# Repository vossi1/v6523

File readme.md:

# V6523 - Replacement for a 6523 or 6525 without IRQ Controller (CBM2 keyboard TPI)  

**Copyright (c) 2024 Vossi - v.1 / v.2 (C64 IEEE option)**

**www.mos6509.com**

## License
This work is licensed under a Creative Commons Attribution-ShareAlike 4.0
International License. See [https://creativecommons.org/licenses/by-sa/4.0/](https://creativecommons.org/licenses/by-sa/4.0/).

:thumbsup: v.2 now with C64 IEEE488 Interface support (use special IEEE hdl-code)!

:pushpin: At JLC you have to select: Remove Order Number = "Specify a location"

**[Schematic](https://github.com/vossi1/v6523/blob/master/v6523_v2.png)**

**[Parts](https://github.com/vossi1/v6523/blob/master/parts.txt)**

**CPLD-Firmware:** The .JED file can be uploaded with a JTAG-SMT2 Xilinx programmer (China) and [xc3sprog](https://xc3sprog.sourceforge.net/)

:exclamation: **BEWARE: I got good CPLD's from China but there are some XC9572XL FAKES out there**

cbm 720 (the very first V6523 on the photo misses the pin1 side notch)

:white_check_mark: **Tested successful in cbm620, 720 and P500 with:** Diagnostic-ROM and my fingers :wink:

:x: **Does not work in 1551, C64-Magic Voice, CDTV (A570)**

You have to solder a wire to pin 10 of the 74LS08 (PHI2): (sadly I forgot the "specify a location" option :wink: )

I added this logic for the IEEE support to the v.2 version:

REASON: Commodore didn't combined CS with PHI2 like in the CBM2 machines.
According to the datasheet for the 6525, they should have done that.
I don't know why it still works with the 6525 in the IEEE interface?

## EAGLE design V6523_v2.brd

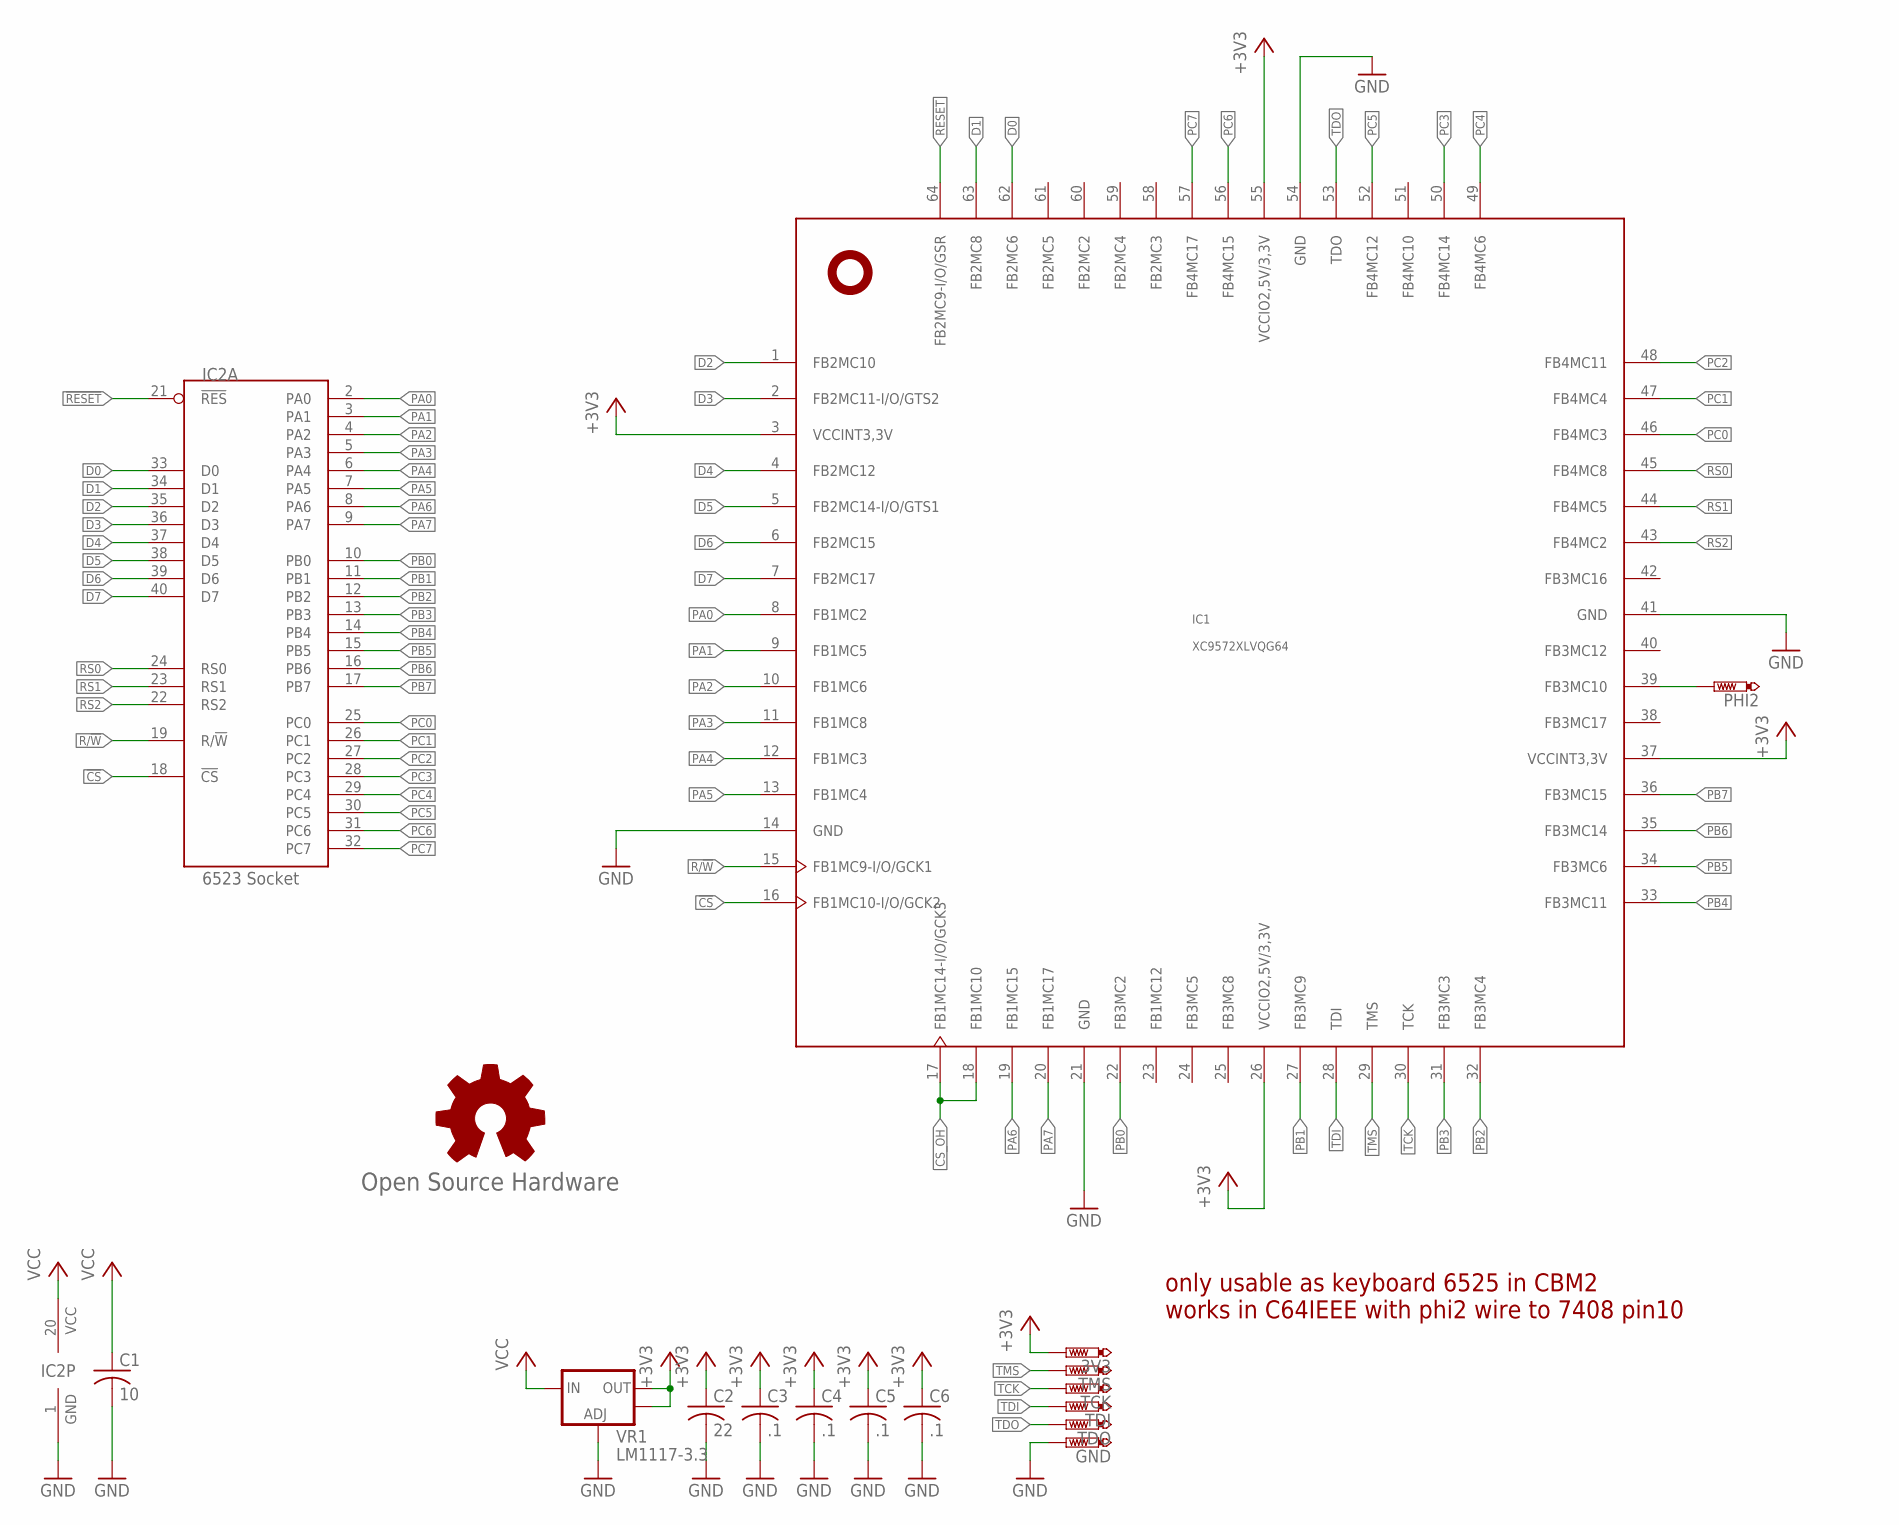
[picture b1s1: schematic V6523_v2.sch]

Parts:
3V3: PTR1TP08R; TP08R
C1: 10; C0805
C2: 22; C0805
C3, C4, C5, C6: .1; C0603
GND: PTR1TP08R; TP08R
GOLD_ORB_SM1: Open Source Hardware; OSHW_5MM
IC1: XC9572XLVQG64; VQFP64
IC2: 6523 Socket; DIL40-RP-NOFRAME
PHI2: PTR1TP08R; TP08R
TCK: PTR1TP08R; TP08R
TDI: PTR1TP08R; TP08R
TDO: PTR1TP08R; TP08R
TMS: PTR1TP08R; TP08R
VR1: LM1117-3.3; SOT223

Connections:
!CS: IC1.16 (FB1MC10-I/O/GCK2), IC2.18 (!CS)
!RESET: IC1.64 (FB2MC9-I/O/GSR), IC2.21 (!RES)
+3V3: 3V3.TP, C2.1, C3.1, C4.1, C5.1, C6.1, IC1.3 (VCCINT3,3V), IC1.26 (VCCIO2,5V/3,3V), IC1.37 (VCCINT3,3V), IC1.55 (VCCIO2,5V/3,3V), VR1.2 (OUT), VR1.4 (OUT)
CS_OH: IC1.17 (FB1MC14-I/O/GCK3), IC1.18 (FB1MC10)
D0: IC1.62 (FB2MC6), IC2.33 (D0)
D1: IC1.63 (FB2MC8), IC2.34 (D1)
D2: IC1.1 (FB2MC10), IC2.35 (D2)
D3: IC1.2 (FB2MC11-I/O/GTS2), IC2.36 (D3)
D4: IC1.4 (FB2MC12), IC2.37 (D4)
D5: IC1.5 (FB2MC14-I/O/GTS1), IC2.38 (D5)
D6: IC1.6 (FB2MC15), IC2.39 (D6)
D7: IC1.7 (FB2MC17), IC2.40 (D7)
GND: C1.2, C2.2, C3.2, C4.2, C5.2, C6.2, GND.TP, IC1.14 (GND), IC1.21 (GND), IC1.41 (GND), IC1.54 (GND), IC2.1 (GND), VR1.1 (ADJ)
PA0: IC1.8 (FB1MC2), IC2.2 (PA0)
PA1: IC1.9 (FB1MC5), IC2.3 (PA1)
PA2: IC1.10 (FB1MC6), IC2.4 (PA2)
PA3: IC1.11 (FB1MC8), IC2.5 (PA3)
PA4: IC1.12 (FB1MC3), IC2.6 (PA4)
PA5: IC1.13 (FB1MC4), IC2.7 (PA5)
PA6: IC1.19 (FB1MC15), IC2.8 (PA6)
PA7: IC1.20 (FB1MC17), IC2.9 (PA7)
PB0: IC1.22 (FB3MC2), IC2.10 (PB0)
PB1: IC1.27 (FB3MC9), IC2.11 (PB1)
PB2: IC1.32 (FB3MC4), IC2.12 (PB2)
PB3: IC1.31 (FB3MC3), IC2.13 (PB3)
PB4: IC1.33 (FB3MC11), IC2.14 (PB4)
PB5: IC1.34 (FB3MC6), IC2.15 (PB5)
PB6: IC1.35 (FB3MC14), IC2.16 (PB6)
PB7: IC1.36 (FB3MC15), IC2.17 (PB7)
PC0: IC1.46 (FB4MC3), IC2.25 (PC0)
PC1: IC1.47 (FB4MC4), IC2.26 (PC1)
PC2: IC1.48 (FB4MC11), IC2.27 (PC2)
PC3: IC1.50 (FB4MC14), IC2.28 (PC3)
PC4: IC1.49 (FB4MC6), IC2.29 (PC4)
PC5: IC1.52 (FB4MC12), IC2.30 (PC5)
PC6: IC1.56 (FB4MC15), IC2.31 (PC6)
PC7: IC1.57 (FB4MC17), IC2.32 (PC7)
PHI2: IC1.39 (FB3MC10), PHI2.TP
R/!W: IC1.15 (FB1MC9-I/O/GCK1), IC2.19 (R/!W)
RS0: IC1.45 (FB4MC8), IC2.24 (RS0)
RS1: IC1.44 (FB4MC5), IC2.23 (RS1)
RS2: IC1.43 (FB4MC2), IC2.22 (RS2)
TCK: IC1.30 (TCK), TCK.TP
TDI: IC1.28 (TDI), TDI.TP
TDO: IC1.53 (TDO), TDO.TP
TMS: IC1.29 (TMS), TMS.TP
VCC: C1.1, IC2.20 (VCC), VR1.3 (IN)

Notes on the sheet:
only usable as keyboard 6525 in CBM2 works in C64IEEE with phi2 wire to 7408 pin10

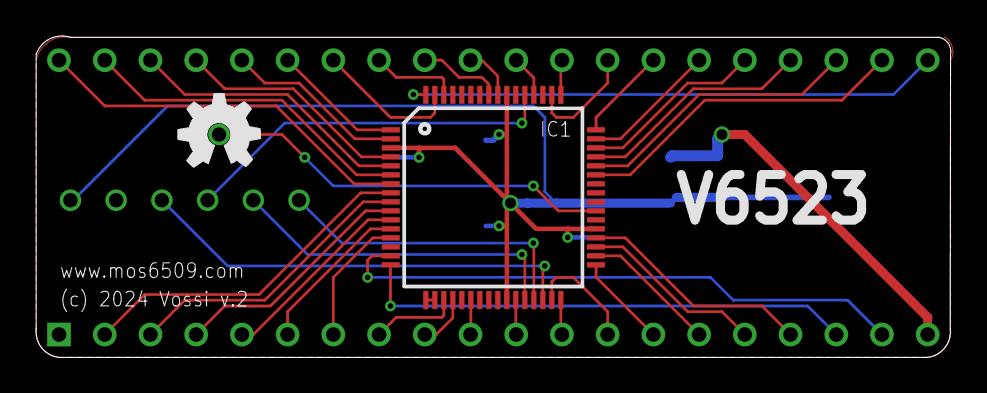
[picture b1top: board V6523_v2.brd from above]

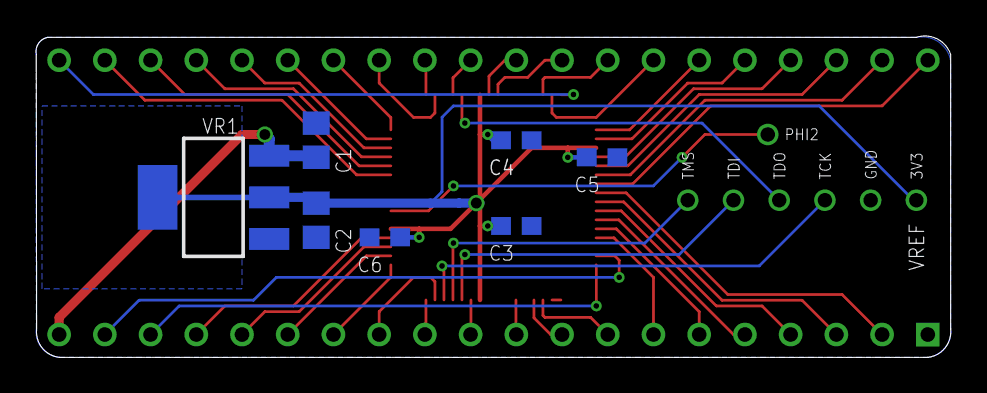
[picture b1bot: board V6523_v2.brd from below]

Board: 2 copper layers, 50.8 x 17.9 mm, 17 parts (13 on the bottom side), 47 nets.

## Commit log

2024-03-08 initial working v1
2024-03-08 initial v1
2024-03-08 added ieee488
2024-03-08 720 photo
2024-03-09 not working in Magic Voice, IEEE
2024-03-09 not working in CDTV
2024-03-09 partlist
2024-03-10 updated cpld order code
2024-04-03 added ieee firmware
2024-04-03 layout with phi2 for c64 ieee interface
2024-04-06 correction in gerbers v2
2024-04-06 v2 phi2 solderpoint for c64 ieee usage
2024-04-06 reuploaded v1 because v2 is not tested
2024-04-06 reuploaded gerber v1 because v2 is not tested
2024-04-12 added 7400 logic pic
2024-04-19 v2 ieee488 support tested
2024-04-19 v2 tested
2024-04-29 special ieee hdl-code
2024-05-03 not working in 1551
2024-06-20 license cc4
2025-01-10 added eagle files
2025-01-10 added firmware programming doc

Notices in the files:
V6523_v2.brd:
(c) 2024 Vossi v.2
parts and their libraries:
SparkFun: Licensing: CC v3.0 Share-Alike You are welcome to use this library for commercial purposes.
